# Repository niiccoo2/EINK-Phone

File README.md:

[Google Doc Notes Link](https://docs.google.com/document/d/1l_P9BNs8-fzjLHjxsxwmtQVHC8uADbmZvHsqvaNpZNw/edit?usp=sharing)
[Docs link for pico version](https://docs.google.com/document/d/1WdVnLDW4LZ5mjuCLy1hVp1n7MNubI6F_SzgGbY42siQ/edit?usp=sharing)

### Sunday, May 11:
* Saw the light phone 3 and thought it cost too much.
* Started thinking about how I could make my own

*30 minutes*

### Monday, May 12:
* Decided to use a pi zero w
* Ordered a SIM7600A-H cell modem.

*30 minutes*

### Thursday, May 15:
* Got modem and started working on the python code that sends texts
* Found out that verizon does not work with my modem
* Thought that ssh was slow bc I was using a pi zero *My fault not true*
* Ordered rpi zero 2w
* Ordered a new sim card
* Ordered a 4.2in Waveshare E-Ink screen

*5 hours*

### Saturday, May 17:
* Started figuring out how to use the display drivers in python
* Got the demo working [Photo](https://photos.app.goo.gl/T3E3aoRRHVqETAhi7)
* Got it so that it would display a random number
* Figured out how to use partial refreshes

*4 hours*

### Sunday, May 18:
*Got a basic homescreen working it will dynamically display apps from a dictionary

*3 hours*

### Tuesday, May 20:
*Added a cursor so you can use input statements to move up and down on the screen and select an app. [Photo](https://photos.app.goo.gl/G6LSFMMkUEmNv3iD8)

*3 hours*

### Thursday, May 22:
* Set up new sim card
* FINALLY got the modem working for texting and data
* Hardwired the usb connection because the cable was too big
* [Blog Post](https://niiccoo2.xyz/raspberry-pi-modems/)

*4 hours*

### Friday, May 23:
* Somehow corrupted my pc by thruning on bluetooth, all I wanted was music
* Started working on the first screen of the messages app [Photo](https://photos.app.goo.gl/84rxM1MTwXnvZ23s9)

*4 hours*

### Saturday, May 24:
* Made it so the convos would dynamically display from the JSON file. [Photo](https://photos.app.goo.gl/KQzkmpvL8ekmdxA4A)
* I (Think?) I added scrolling to the convo view today (still has bugs)

*4 hours*

### Sunday, May 25:
* Added the message view
* Made it so it will refresh if you get a new message or send one
* Saves sent and recived messages to the JSON file
* TEXT WRAPPING!!!
* Write text to the left OR the right side of the screen. [Photo](https://photos.app.goo.gl/zQqkJZknWvvdAGR4A)

*6 hours*

### Monday, May 26:
* Made a bad YouTube video about the phone, got almost 3k views for first video

### Thursday, May 29:
* Added scrolling to the message view
* Got idea to make custom PCB for the keyboard

*2 hours*

### Friday, May 30:
* Started learning KiCad and designing the PCB schematic

*5 hours*

### Saturday, May 31:
* HACKNIGHT!
* Worked on the Keyboard pcb a bit

*1 hour*

### Sunday, June 1:
* HACKNIGHT!

### Monday June 2:
* Wired the PCB in KiCad
* Ordered PCB from PcbWay
* Ordered parts from digikey
* Forgot power connecter on PCB (Not the end of the world)

*4 hours*

### Saturday, June 7:
* Tried to get the modem to call my phone, having issues
* Made an account on some b2b site to update firmware.

*2 hours*

# Highway project starts here:
I worked on this a bunch with my own time and money. I got a ok prototype but I'm deciding to change to a custom pcb and using the SIM7000G so that the final device will be much smaller.

### Tuesday, June 17:
* Decided to change from using a pi zero 2 to a pi pico
* Pi pico will use much less power
* Using a SIM7000G modem
* Making a custom PCB

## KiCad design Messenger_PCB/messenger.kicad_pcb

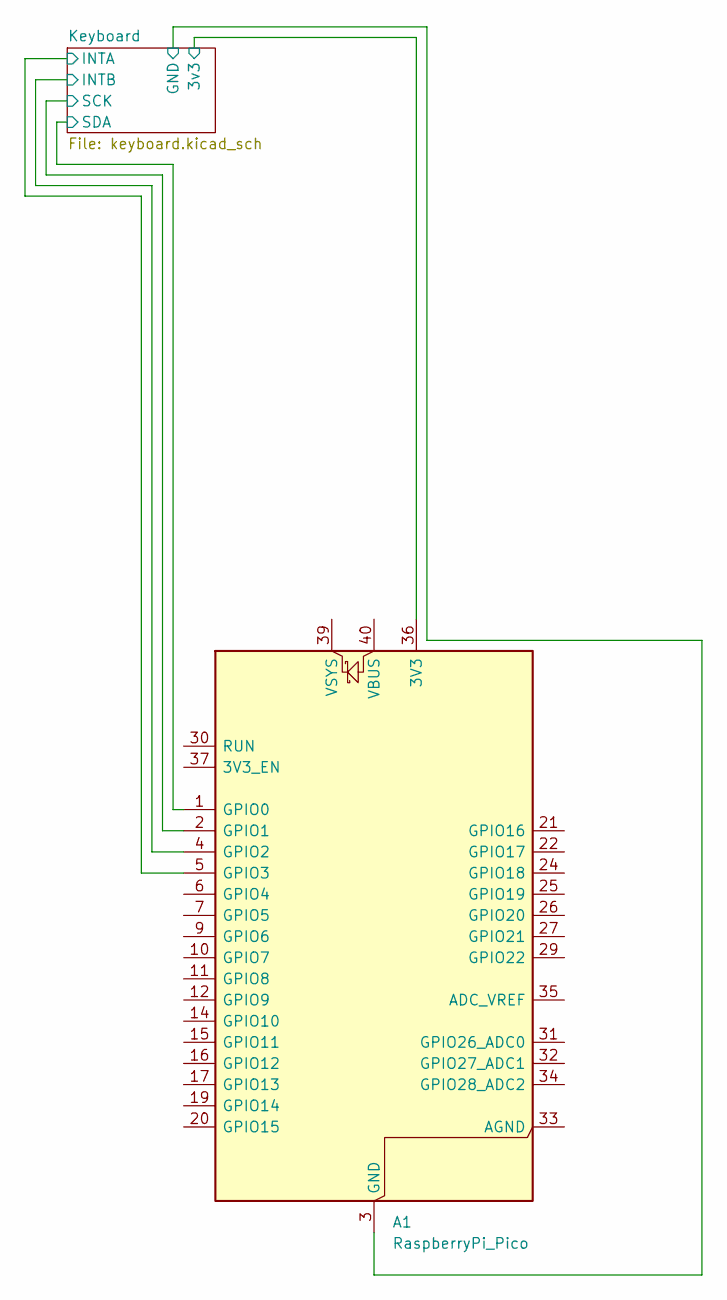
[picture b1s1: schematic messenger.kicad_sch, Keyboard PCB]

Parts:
A1: RaspberryPi_Pico; RaspberryPi_Pico_Common_Unspecified

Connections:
unnamed: A1.3 (GND), A1.8 (GND), A1.13 (GND), A1.18 (GND), A1.23 (GND), A1.28 (GND), A1.38 (GND)

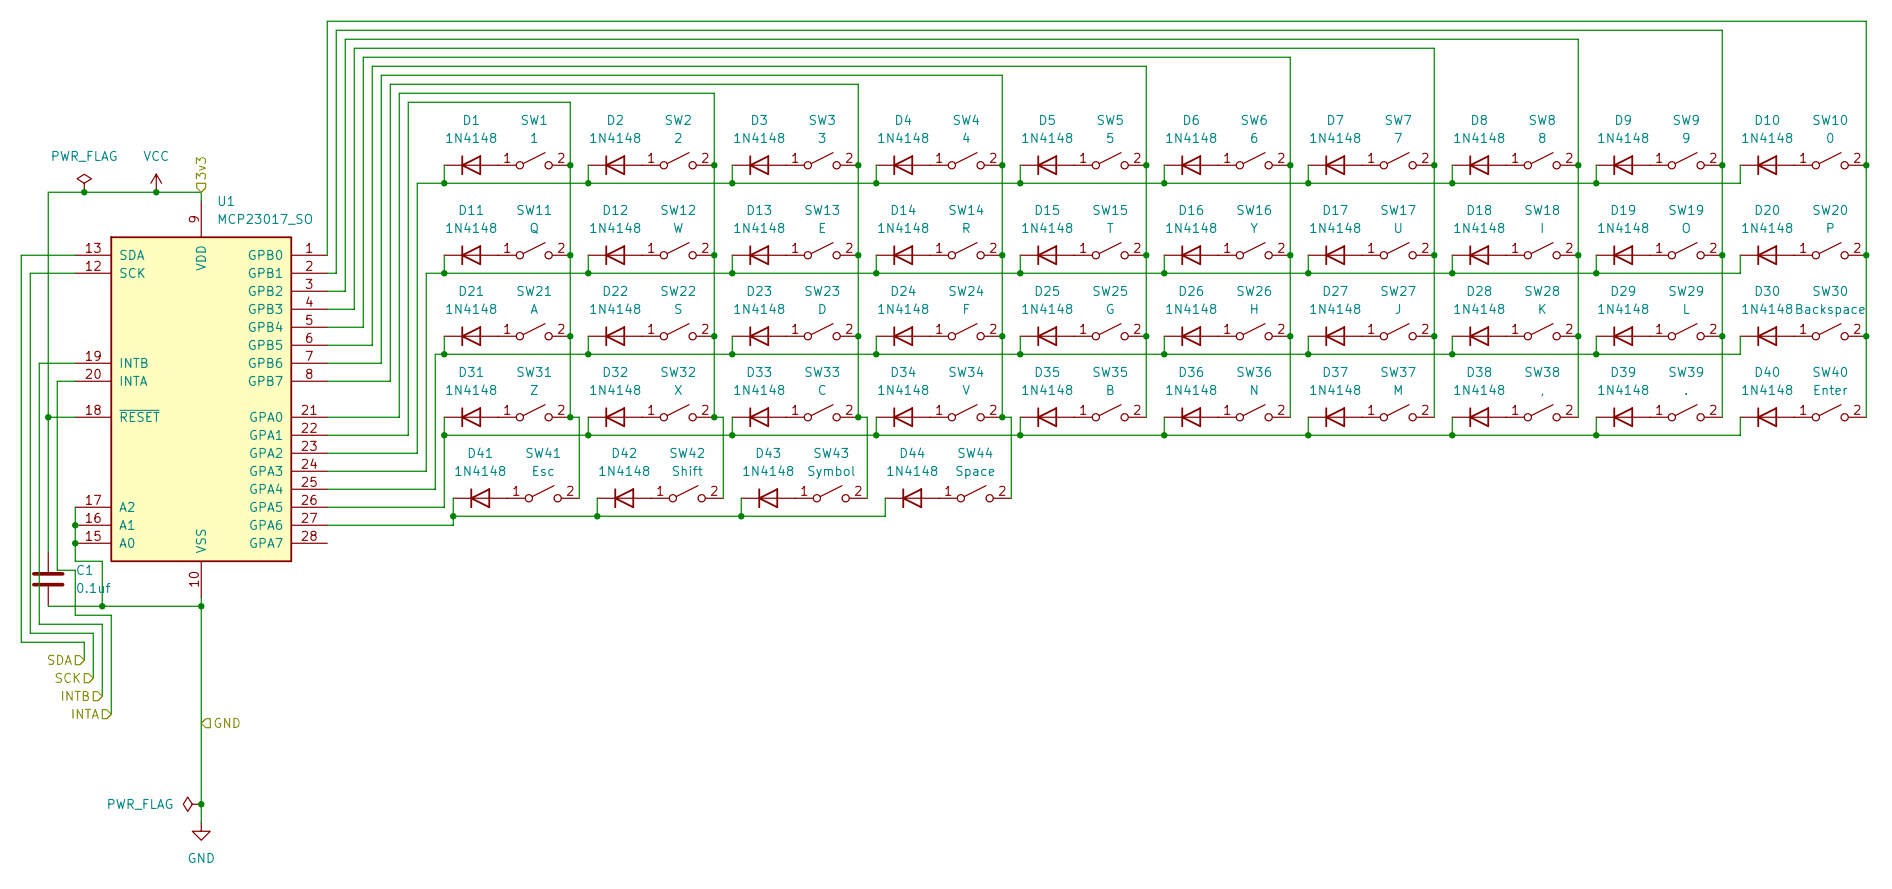
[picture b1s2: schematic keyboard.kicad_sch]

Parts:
C1: 0.1uf; C_Disc_D5.0mm_W2.5mm_P5.00mm
D1, D2, D3, D4, D5, D6, D7, D8, D9, D10, D11, D12, D13, D14, D15, D16, D17, D18, D19, D20, D21, D22, D23, D24, D25, D26, D27, D28, D29, D30, D31, D32, D33, D34, D35, D36, D37, D38, D39, D40, D41, D42, D43, D44: 1N4148; D_SOD-323_HandSoldering
SW1: 1; SON4_PTS526 SM15 SMTR2 LFS_CNK FLIPPED PINS
SW2: 2; SON4_PTS526 SM15 SMTR2 LFS_CNK FLIPPED PINS
SW3: 3; SON4_PTS526 SM15 SMTR2 LFS_CNK FLIPPED PINS
SW4: 4; SON4_PTS526 SM15 SMTR2 LFS_CNK FLIPPED PINS
SW5: 5; SON4_PTS526 SM15 SMTR2 LFS_CNK FLIPPED PINS
SW6: 6; SON4_PTS526 SM15 SMTR2 LFS_CNK FLIPPED PINS
SW7: 7; SON4_PTS526 SM15 SMTR2 LFS_CNK FLIPPED PINS
SW8: 8; SON4_PTS526 SM15 SMTR2 LFS_CNK FLIPPED PINS
SW9: 9; SON4_PTS526 SM15 SMTR2 LFS_CNK FLIPPED PINS
SW10: 0; SON4_PTS526 SM15 SMTR2 LFS_CNK FLIPPED PINS
SW11: Q; SON4_PTS526 SM15 SMTR2 LFS_CNK FLIPPED PINS
SW12: W; SON4_PTS526 SM15 SMTR2 LFS_CNK FLIPPED PINS
SW13: E; SON4_PTS526 SM15 SMTR2 LFS_CNK FLIPPED PINS
SW14: R; SON4_PTS526 SM15 SMTR2 LFS_CNK FLIPPED PINS
SW15: T; SON4_PTS526 SM15 SMTR2 LFS_CNK FLIPPED PINS
SW16: Y; SON4_PTS526 SM15 SMTR2 LFS_CNK FLIPPED PINS
SW17: U; SON4_PTS526 SM15 SMTR2 LFS_CNK FLIPPED PINS
SW18: I; SON4_PTS526 SM15 SMTR2 LFS_CNK FLIPPED PINS
SW19: O; SON4_PTS526 SM15 SMTR2 LFS_CNK FLIPPED PINS
SW20: P; SON4_PTS526 SM15 SMTR2 LFS_CNK FLIPPED PINS
SW21: A; SON4_PTS526 SM15 SMTR2 LFS_CNK FLIPPED PINS
SW22: S; SON4_PTS526 SM15 SMTR2 LFS_CNK FLIPPED PINS
SW23: D; SON4_PTS526 SM15 SMTR2 LFS_CNK FLIPPED PINS
SW24: F; SON4_PTS526 SM15 SMTR2 LFS_CNK FLIPPED PINS
SW25: G; SON4_PTS526 SM15 SMTR2 LFS_CNK FLIPPED PINS
SW26: H; SON4_PTS526 SM15 SMTR2 LFS_CNK FLIPPED PINS
SW27: J; SON4_PTS526 SM15 SMTR2 LFS_CNK FLIPPED PINS
SW28: K; SON4_PTS526 SM15 SMTR2 LFS_CNK FLIPPED PINS
SW29: L; SON4_PTS526 SM15 SMTR2 LFS_CNK FLIPPED PINS
SW30: Backspace; SON4_PTS526 SM15 SMTR2 LFS_CNK FLIPPED PINS
SW31: Z; SON4_PTS526 SM15 SMTR2 LFS_CNK FLIPPED PINS
SW32: X; SON4_PTS526 SM15 SMTR2 LFS_CNK FLIPPED PINS
SW33: C; SON4_PTS526 SM15 SMTR2 LFS_CNK FLIPPED PINS
SW34: V; SON4_PTS526 SM15 SMTR2 LFS_CNK FLIPPED PINS
SW35: B; SON4_PTS526 SM15 SMTR2 LFS_CNK FLIPPED PINS
SW36: N; SON4_PTS526 SM15 SMTR2 LFS_CNK FLIPPED PINS
SW37: M; SON4_PTS526 SM15 SMTR2 LFS_CNK FLIPPED PINS
SW38: ,; SON4_PTS526 SM15 SMTR2 LFS_CNK FLIPPED PINS
SW39: .; SON4_PTS526 SM15 SMTR2 LFS_CNK FLIPPED PINS
SW40: Enter; SON4_PTS526 SM15 SMTR2 LFS_CNK FLIPPED PINS
SW41: Esc; SON4_PTS526 SM15 SMTR2 LFS_CNK FLIPPED PINS
SW42: Shift; SON4_PTS526 SM15 SMTR2 LFS_CNK FLIPPED PINS
SW43: Symbol; SON4_PTS526 SM15 SMTR2 LFS_CNK FLIPPED PINS
SW44: Space; SON4_PTS526 SM15 SMTR2 LFS_CNK FLIPPED PINS
U1: MCP23017_SO; SOIC-28W_7.5x17.9mm_P1.27mm

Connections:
GND: C1.2, U1.10 (VSS), U1.15 (A0), U1.16 (A1), U1.17 (A2); also elsewhere on the board
unnamed: D1.2 (A), SW1.1 (A)
unnamed: D1.1 (K), D2.1 (K), D3.1 (K), D4.1 (K), D5.1 (K), D6.1 (K), D7.1 (K), D8.1 (K), D9.1 (K), D10.1 (K), U1.23 (GPA2)
unnamed: D2.2 (A), SW2.1 (A)
unnamed: D3.2 (A), SW3.1 (A)
unnamed: D4.2 (A), SW4.1 (A)
unnamed: D5.2 (A), SW5.1 (A)
unnamed: D6.2 (A), SW6.1 (A)
unnamed: D7.2 (A), SW7.1 (A)
unnamed: D8.2 (A), SW8.1 (A)
unnamed: D9.2 (A), SW9.1 (A)
unnamed: D10.2 (A), SW10.1 (A)
unnamed: D11.2 (A), SW11.1 (A)
unnamed: D11.1 (K), D12.1 (K), D13.1 (K), D14.1 (K), D15.1 (K), D16.1 (K), D17.1 (K), D18.1 (K), D19.1 (K), D20.1 (K), U1.24 (GPA3)
unnamed: D12.2 (A), SW12.1 (A)
unnamed: D13.2 (A), SW13.1 (A)
unnamed: D14.2 (A), SW14.1 (A)
unnamed: D15.2 (A), SW15.1 (A)
unnamed: D16.2 (A), SW16.1 (A)
unnamed: D17.2 (A), SW17.1 (A)
unnamed: D18.2 (A), SW18.1 (A)
unnamed: D19.2 (A), SW19.1 (A)
unnamed: D20.2 (A), SW20.1 (A)
unnamed: D21.2 (A), SW21.1 (A)
unnamed: D21.1 (K), D22.1 (K), D23.1 (K), D24.1 (K), D25.1 (K), D26.1 (K), D27.1 (K), D28.1 (K), D29.1 (K), D30.1 (K), U1.25 (GPA4)
unnamed: D22.2 (A), SW22.1 (A)
unnamed: D23.2 (A), SW23.1 (A)
unnamed: D24.2 (A), SW24.1 (A)
unnamed: D25.2 (A), SW25.1 (A)
unnamed: D26.2 (A), SW26.1 (A)
unnamed: D27.2 (A), SW27.1 (A)
unnamed: D28.2 (A), SW28.1 (A)
unnamed: D29.2 (A), SW29.1 (A)
unnamed: D30.2 (A), SW30.1 (A)
unnamed: D31.2 (A), SW31.1 (A)
unnamed: D31.1 (K), D32.1 (K), D33.1 (K), D34.1 (K), D35.1 (K), D36.1 (K), D37.1 (K), D38.1 (K), D39.1 (K), D40.1 (K), U1.26 (GPA5)
unnamed: D32.2 (A), SW32.1 (A)
unnamed: D33.2 (A), SW33.1 (A)
unnamed: D34.2 (A), SW34.1 (A)
unnamed: D35.2 (A), SW35.1 (A)
unnamed: D36.2 (A), SW36.1 (A)
unnamed: D37.2 (A), SW37.1 (A)
unnamed: D38.2 (A), SW38.1 (A)
unnamed: D39.2 (A), SW39.1 (A)
unnamed: D40.2 (A), SW40.1 (A)
unnamed: D41.2 (A), SW41.1 (A)
unnamed: D41.1 (K), D42.1 (K), D43.1 (K), D44.1 (K), U1.27 (GPA6)
unnamed: D42.2 (A), SW42.1 (A)
unnamed: D43.2 (A), SW43.1 (A)
unnamed: D44.2 (A), SW44.1 (A)
unnamed 52: U1.20 (INTA); also elsewhere on the board
unnamed 53: U1.19 (INTB); also elsewhere on the board
unnamed 54: U1.12 (SCK); also elsewhere on the board
unnamed 55: U1.13 (SDA); also elsewhere on the board
unnamed: SW1.2 (B), SW11.2 (B), SW21.2 (B), SW31.2 (B), SW41.2 (B), U1.22 (GPA1)
unnamed: SW10.2 (B), SW20.2 (B), SW30.2 (B), SW40.2 (B), U1.1 (GPB0)
unnamed: SW2.2 (B), SW12.2 (B), SW22.2 (B), SW32.2 (B), SW42.2 (B), U1.21 (GPA0)
unnamed: SW3.2 (B), SW13.2 (B), SW23.2 (B), SW33.2 (B), SW43.2 (B), U1.8 (GPB7)
unnamed: SW4.2 (B), SW14.2 (B), SW24.2 (B), SW34.2 (B), SW44.2 (B), U1.7 (GPB6)
unnamed: SW5.2 (B), SW15.2 (B), SW25.2 (B), SW35.2 (B), U1.6 (GPB5)
unnamed: SW6.2 (B), SW16.2 (B), SW26.2 (B), SW36.2 (B), U1.5 (GPB4)
unnamed: SW7.2 (B), SW17.2 (B), SW27.2 (B), SW37.2 (B), U1.4 (GPB3)
unnamed: SW8.2 (B), SW18.2 (B), SW28.2 (B), SW38.2 (B), U1.3 (GPB2)
unnamed: SW9.2 (B), SW19.2 (B), SW29.2 (B), SW39.2 (B), U1.2 (GPB1)
unnamed 66: U1.28 (GPA7); also elsewhere on the board
VCC: C1.1, U1.9 (VDD), U1.18 (~RESET)

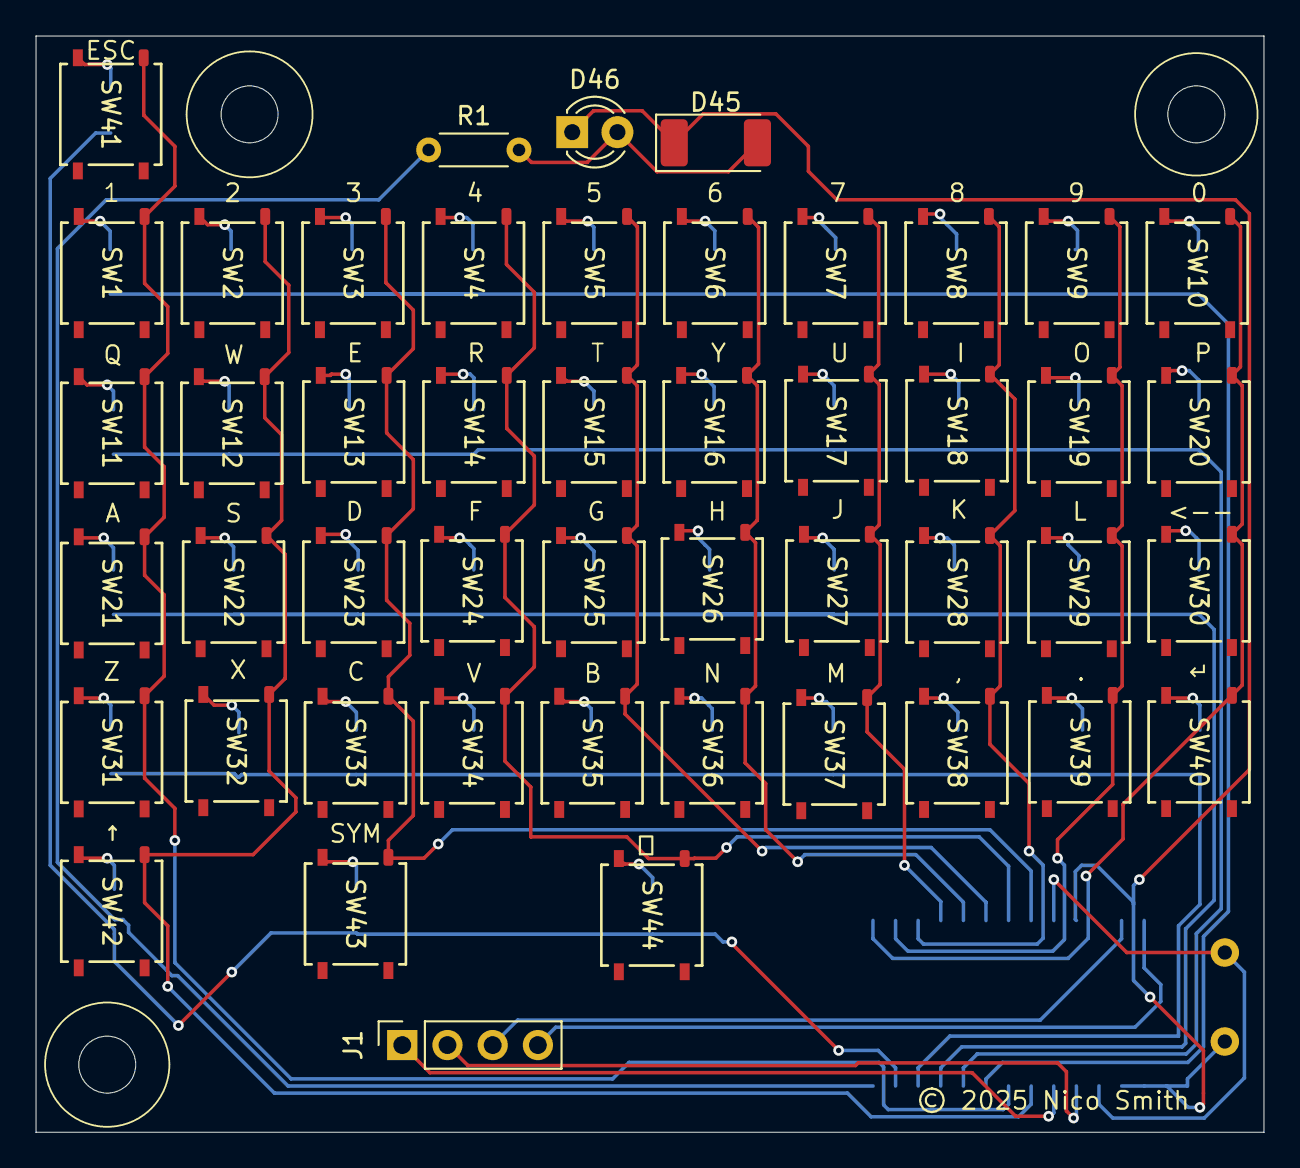
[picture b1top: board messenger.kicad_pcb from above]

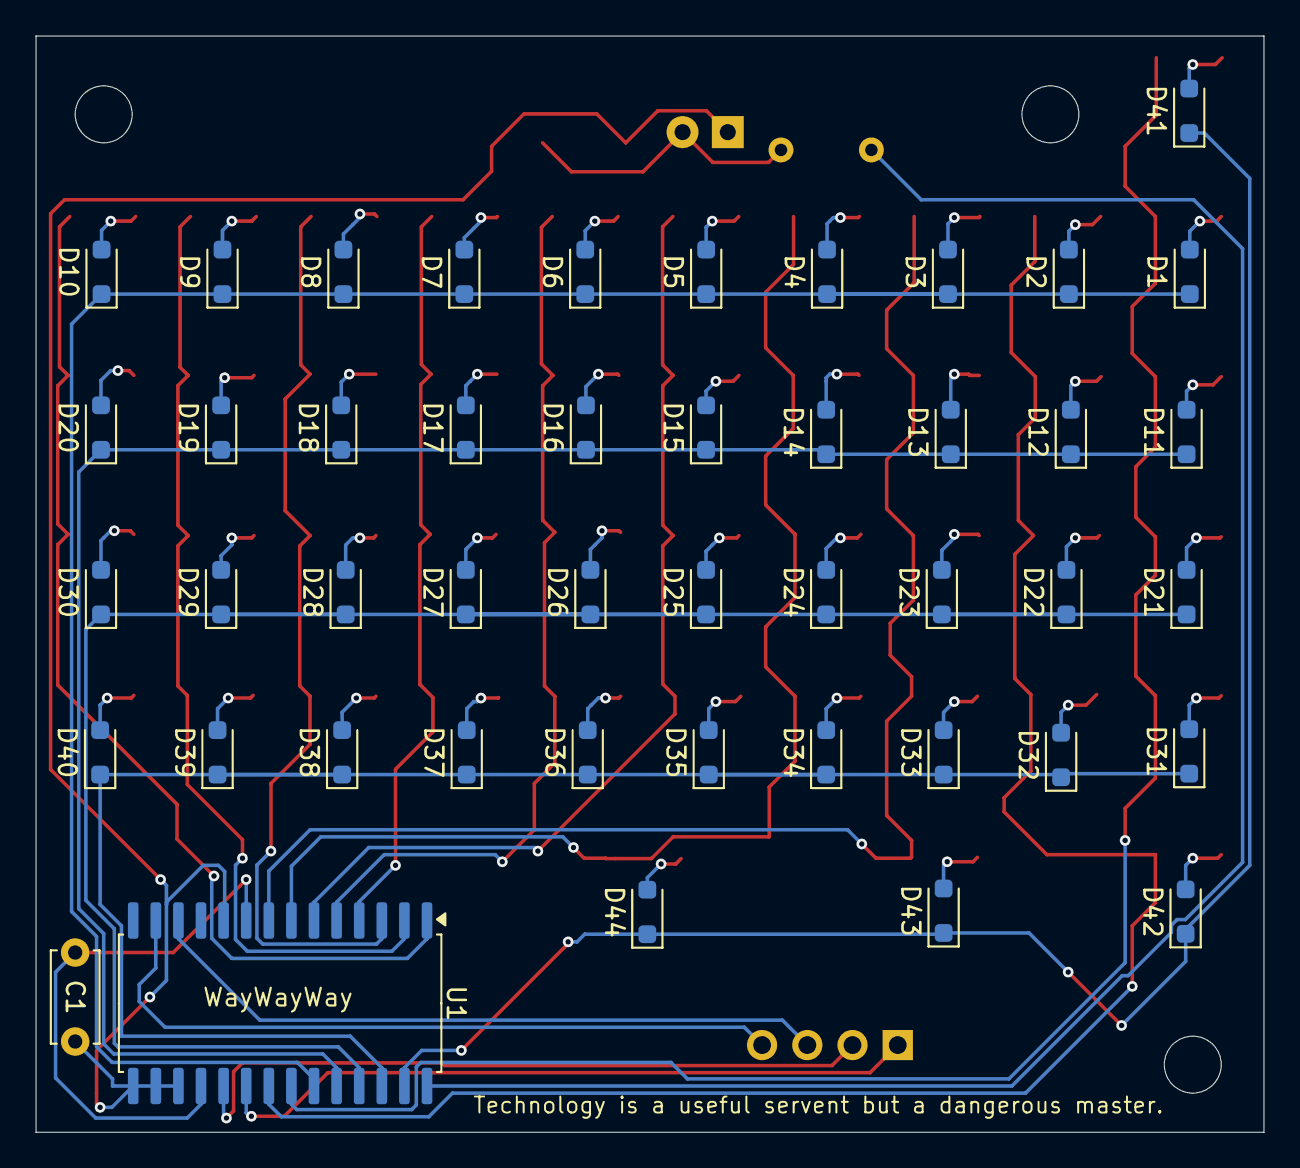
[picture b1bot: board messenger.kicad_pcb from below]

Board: 2 copper layers, 69.0 x 61.6 mm, 94 parts (46 on the bottom side), 67 nets.

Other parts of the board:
D45: LED; LED_2010_5025Metric_Pad1.52x2.65mm_HandSolder
D46: LED; LED_D3.0mm
J1: Conn_01x04_Socket; PinSocket_1x04_P2.54mm_Vertical
R1: R_US; R_Axial_DIN0204_L3.6mm_D1.6mm_P5.08mm_Horizontal

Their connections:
GND: D45.1 (K), D46.1 (K); also elsewhere on the board
unnamed: D45.2 (A), D46.2 (A), R1.2
unnamed 52: J1.1; also elsewhere on the board
unnamed 53: J1.2; also elsewhere on the board
unnamed 54: J1.3; also elsewhere on the board
unnamed 55: J1.4; also elsewhere on the board
unnamed 66: R1.1; also elsewhere on the board

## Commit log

2025-05-12 Inital commit
2025-05-17 Added libarys
2025-05-17 change
2025-05-18 Got screen to draw text
2025-05-19 test
2025-05-19 added for loop that draws apps to screen
2025-05-20 added the selector
2025-05-20 school
2025-05-20 working on modem code
2025-05-21 added the ability to open apps
2025-05-22 I was on wrong device
2025-05-22 added save message function
2025-05-24 worked on messages app
2025-05-24 got dynamic messages working
2025-05-25 added scrolling to messages
2025-05-26 added draw with wrap
2025-05-26 kinda got scrolling working
2025-06-17 Remove project journal and temporary image; add README.md
    Delete JOURNAL.md and a temporary image file to clean up the repository. Add README.md to provide project documentation and improve clarity for contributors.
2025-06-18 Added KiCad data
2025-06-18 Replace Messenger PCB files with EINK-Phone PCB project
    Remove Messenger PCB design and backup files, and add new EINK-Phone KiCad project files to transition development focus to the EINK-Phone hardware.
2025-06-18 Add thermistor symbol to schematic; remove old backups and project file
    - Added "Device:Thermistor_US" symbol to EINK-Phone.kicad_sch for temperature sensing support
    - Deleted outdated backup ZIP and messenger.kicad_pro project file
    - Prepared new backup directory for updated project structure
2025-06-20 Increase maxBuffer size to prevent stdout overflow errors
2025-06-20 Add fp-info-cache to track footprint information in PCB directory.

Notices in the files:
Messenger_PCB/messenger.kicad_pcb:
© 2025 Nico Smith
